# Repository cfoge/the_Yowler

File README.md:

# the_Yowler
If you find this usefull and would like to pay it forward you can do so here 
XXXXXXXXXXXXXXXXXXXXXXXXXXXXXXXX

WARNING!!!!! Please be aware of the risks asociated with electronics and take the relivant percautuions.

XXXXXXXXXXXXXXXXXXXXXXXXXXXXXXXX

An open source noise maker that saw its life as a Kickstarter product in 2017 and has now become open.

[Mouser BOM cart](https://au.mouser.com/ProjectManager/ProjectDetail.aspx?AccessID=0d14517efb)

The design originates from this kickstarter: https://www.kickstarter.com/projects/218568730/the-yowler-a-community-built-diy-noise-synth
and features:
4 square wave oscilators with knobs and switchible ldr's
3 xor gates used to mix the signals
1 primitive vca made from back to back diodes
a rc low pass filter
a decay cap 
trigger button/jack
sterio/mono out
built in speaker

Please use the design files and ideas in this project to make your own stuff, and share your designs and creations with others.
If you come up with any great ideas or mods, please tell me so i can roll good ideas back into the main design.

Cheers

Rob

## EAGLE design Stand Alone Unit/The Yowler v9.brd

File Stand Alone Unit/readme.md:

These are the designs for the standalone (not eurorack or any other system) Yowler noise machine.

The design originates from this kickstarter: https://www.kickstarter.com/projects/218568730/the-yowler-a-community-built-diy-noise-synth
and features:
4 square wave oscilators with knobs and switchible ldr's
3 xor gates used to mix the signals
1 primitive vca made from back to back diodes
a rc low pass filter
a decay cap 
trigger button/jack
sterio/mono out
built in speaker

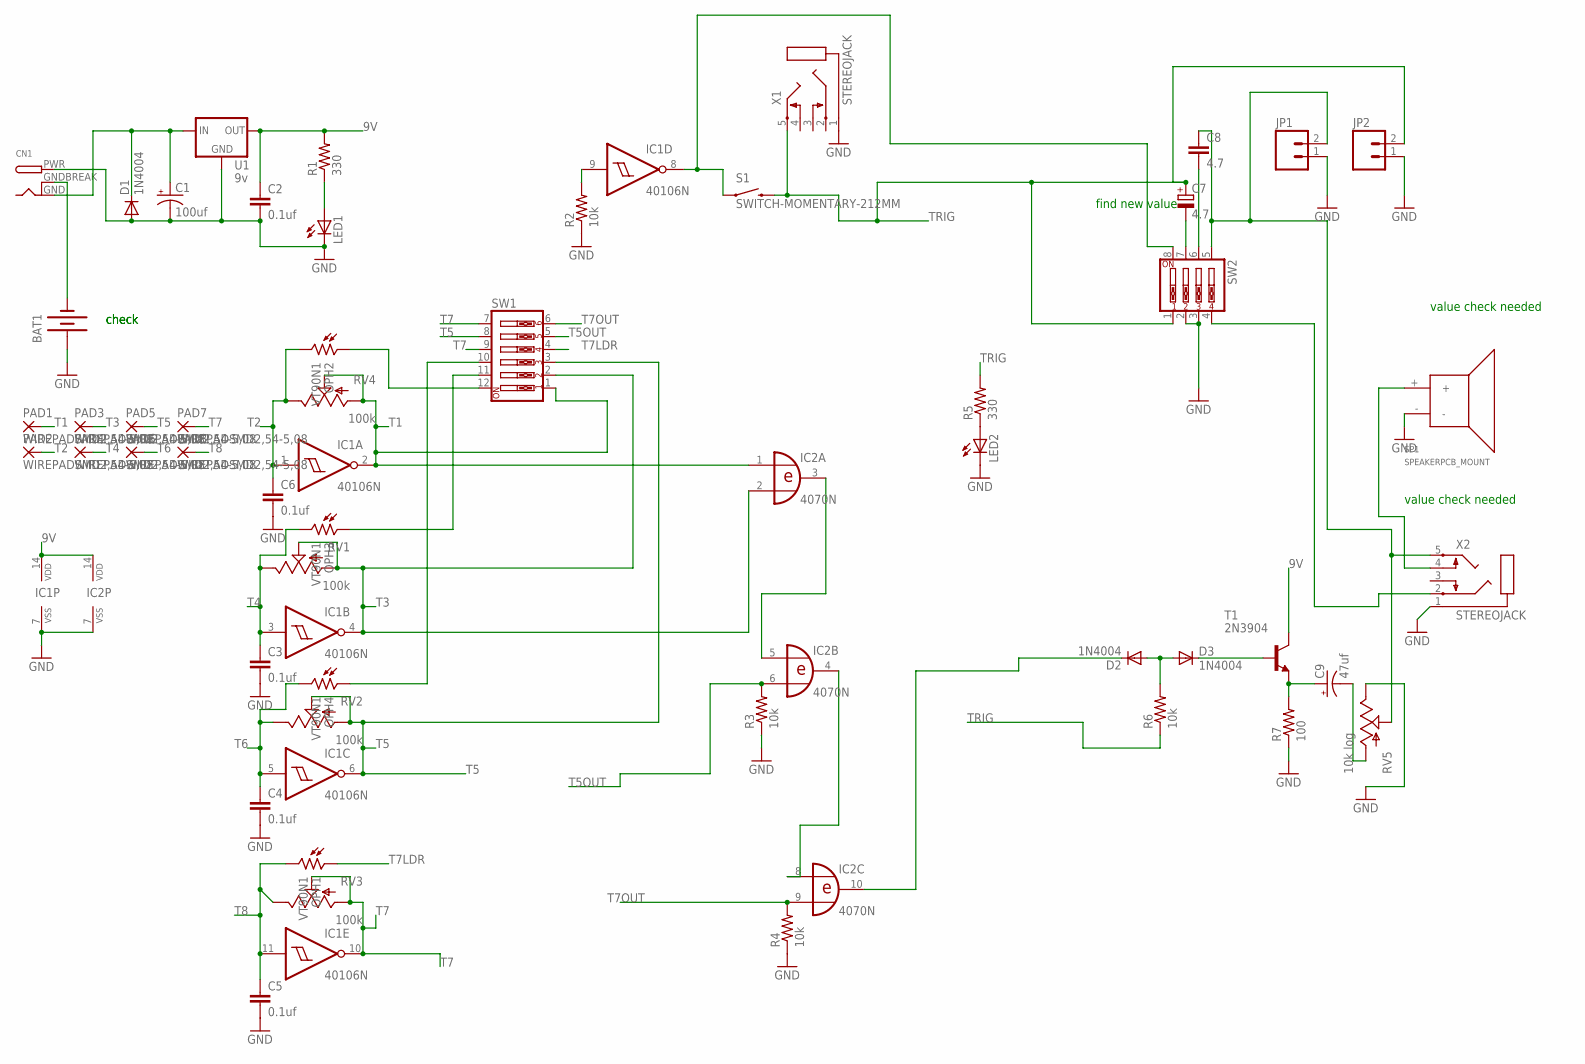
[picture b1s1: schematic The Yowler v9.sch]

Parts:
BAT1: BATTERY9V; BATTCON_9V
C1: 100uf; E5-6
C2, C3, C4, C5, C6: 0.1uf; CAP-PTH-5MM
C7: 4.7; E5-5
C8: 4.7; C050-030X075
C9: 47uf; CPOL-RADIAL-10UF-25V
CN1: DCBARRELPTH; DCJACK_2MM_PTH
D1, D2, D3: 1N4004; DO41-10
IC1: 40106N; DIL14
IC2: 4070N; DIL14
JP1, JP2: M02POGO_PIN_HOLES_ONLY; 1X02_PP_HOLES_ONLY
LED1, LED2: LED3MM
OPH1, OPH2, OPH3, OPH4: VT90N1; VT900
PAD1, PAD2, PAD3, PAD4, PAD5, PAD6, PAD7, PAD8: WIREPADSMD2,54-5,08; SMD2,54-5,08
R1, R5: 330; AXIAL-0.4
R2, R3, R4, R6: 10k; AXIAL-0.4
R7: 100; AXIAL-0.4
RV1, RV2, RV3, RV4: 100k; ALPS_POT
RV5: 10k log; ALPS_POT
S1: SWITCH-MOMENTARY-212MM; TACTILE-PTH-12MM
SP1: SPEAKERPCB_MOUNT; PCB_MOUNT_SPEAKER
SW1: SW_DIP-6; EDG-06
SW2: SW_DIP-4; EDG-04
T1: 2N3904; TO92
U1: 9v; TO-220-ALT
X1, X2: STEREOJACK; STX3100

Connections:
9V: C2.1, IC1.14 (VDD), IC2.14 (VDD), R1.P$2 (2), T1.1 (C), U1.OUT
AUDIO: SW2.4, X2.2
GND: BAT1.+, C1.-, C2.2, C3.2, C4.2, C5.2, C6.2, CN1.PWR, D1.A, IC1.7 (VSS), IC2.7 (VSS), JP1.1, JP2.1, LED1.K (C), LED2.K (C), R2.P$1 (1), R3.P$1 (1), R4.P$1 (1), R7.P$1 (1), RV5.P$1 (E), SP1.-, SW2.2, SW2.3, U1.GND, X1.1, X2.1
unnamed: LED2.A, R5.P$1 (1)
unnamed: IC1.9 (I), R2.P$2 (2)
unnamed: OPH4.1, SW1.10
unnamed: IC2.4 (O), IC2.8 (I0)
unnamed: C9.2 (-), RV5.P$3 (A)
unnamed: C1.+, CN1.GND, D1.C, U1.IN
unnamed: LED1.A, R1.P$1 (1)
unnamed: IC2.3 (O), IC2.5 (I0)
unnamed: OPH2.1, SW1.12
unnamed: IC1.8 (O), S1.1, SW2.8
unnamed: OPH3.1, SW1.11
unnamed: BAT1.-, CN1.GNDBREAK
unnamed: C8.2, SW2.6
unnamed: D2.C, IC2.10 (O)
unnamed: D2.A, D3.A, R6.P$2 (2)
unnamed: C7.-, SW2.7
unnamed: D3.C, T1.2 (B)
unnamed: C9.1 (+), R7.P$2 (2), T1.3 (E)
unnamed: C8.1, JP1.2, RV5.P$2 (S), SW2.5, X2.5
unnamed: SP1.+, X2.4
T1: IC1.2 (O), IC2.1 (I0), PAD1.1, RV4.P$2 (S), RV4.P$3 (A), SW1.1
T2: C6.1, IC1.1 (I), OPH2.2, PAD2.1, RV4.P$1 (E)
T3: IC1.4 (O), IC2.2 (I1), PAD3.1, RV1.P$2 (S), RV1.P$3 (A), SW1.2
T4: C3.1, IC1.3 (I), OPH3.2, PAD4.1, RV1.P$1 (E)
T5: IC1.6 (O), PAD5.1, RV2.P$2 (S), RV2.P$3 (A), SW1.3, SW1.8
T5OUT: IC2.6 (I1), R3.P$2 (2), SW1.5
T6: C4.1, IC1.5 (I), OPH4.2, PAD6.1, RV2.P$1 (E)
T7: IC1.10 (O), PAD7.1, RV3.P$2 (S), RV3.P$3 (A), SW1.7, SW1.9
T7LDR: OPH1.1, SW1.4
T7OUT: IC2.9 (I1), R4.P$2 (2), SW1.6
T8: C5.1, IC1.11 (I), OPH1.2, PAD8.1, RV3.P$1 (E)
TRIG: C7.+, JP2.2, R5.P$2 (2), R6.P$1 (1), S1.3 (2), SW2.1, X1.5

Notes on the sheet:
check
value check needed
find new value

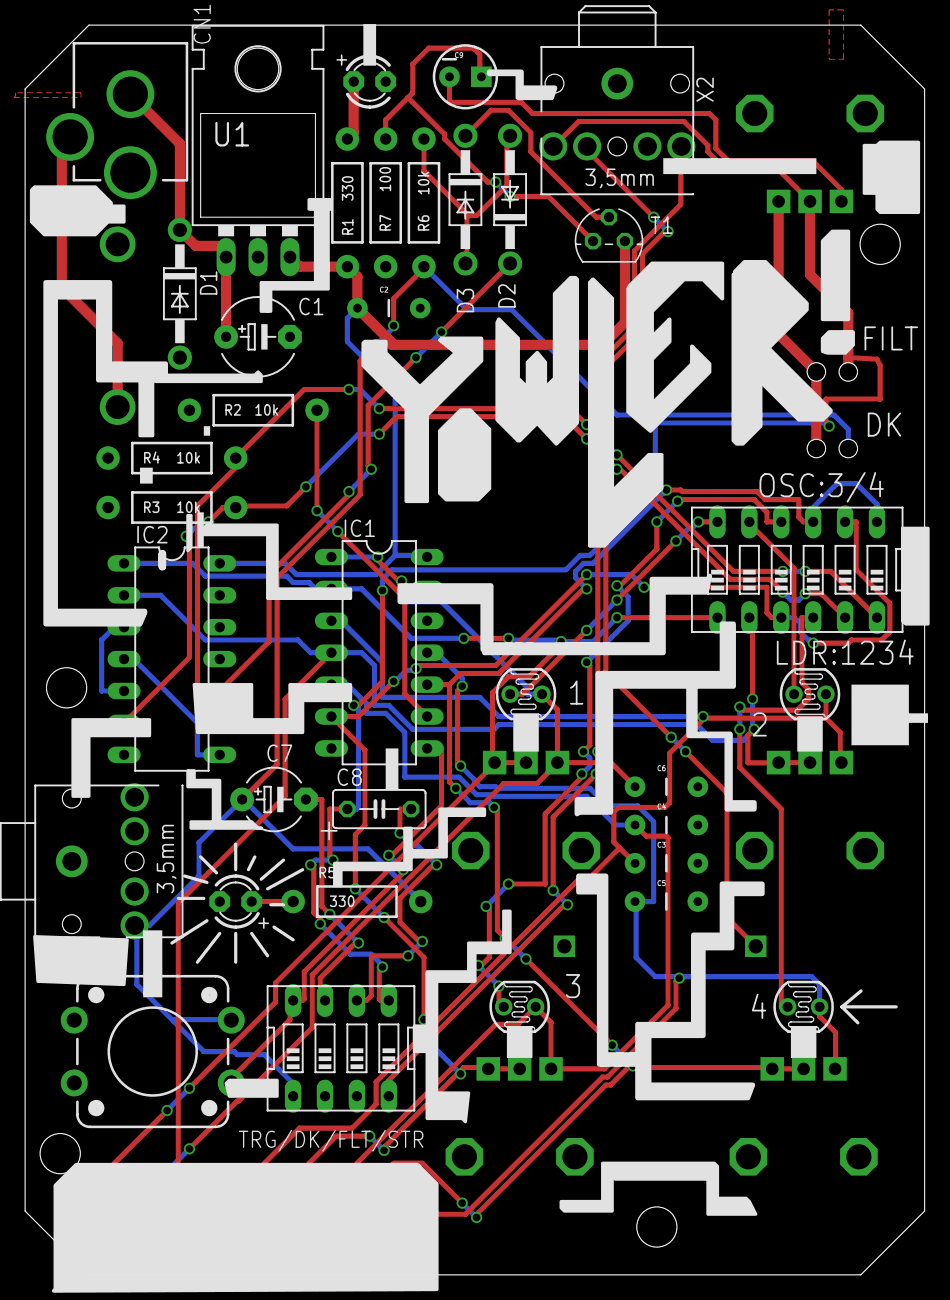
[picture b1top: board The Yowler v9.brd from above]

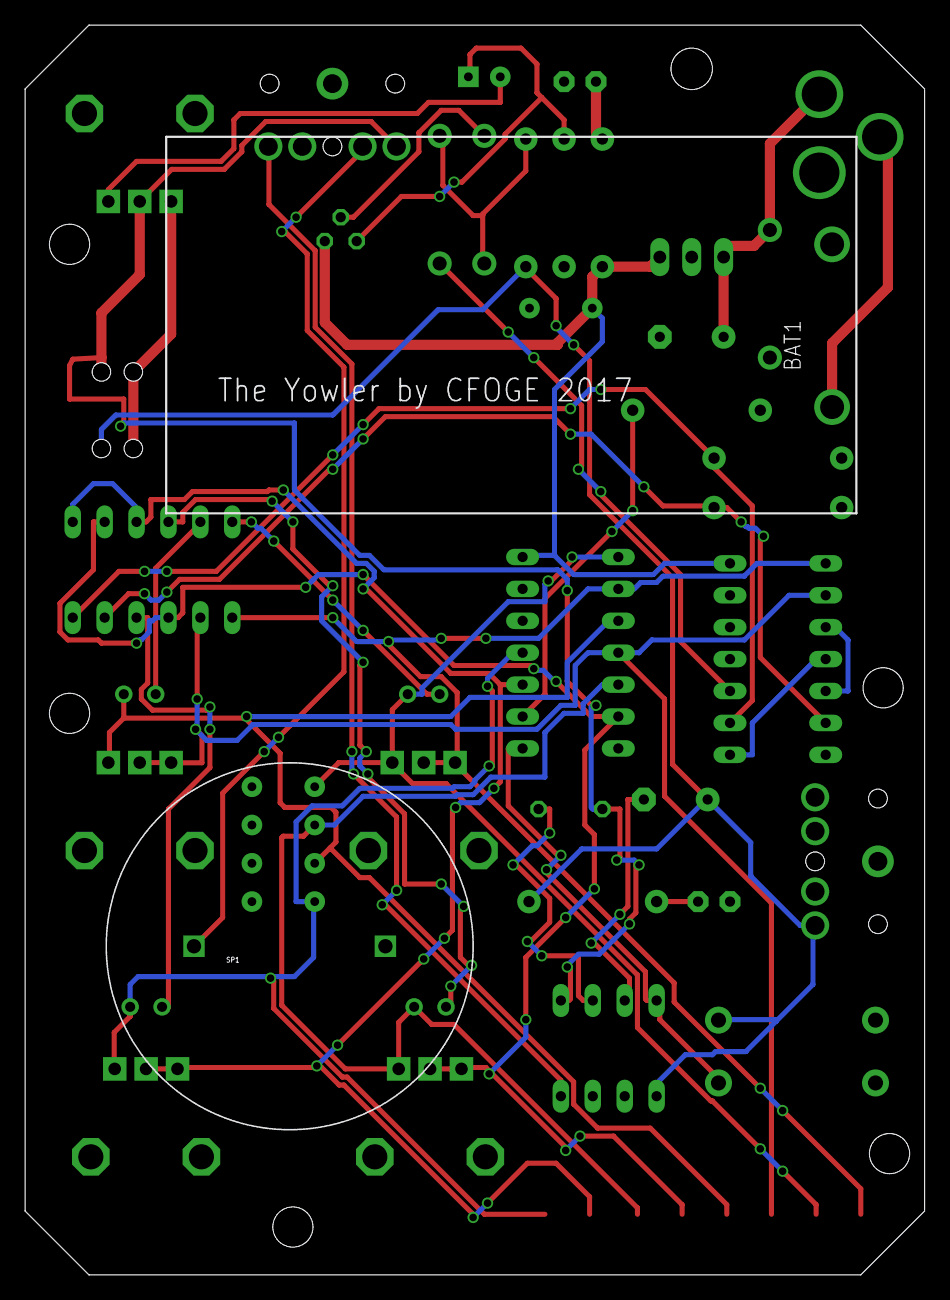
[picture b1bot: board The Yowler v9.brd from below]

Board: 2 copper layers, 71.6 x 99.5 mm, 52 parts (2 on the bottom side), 35 nets.

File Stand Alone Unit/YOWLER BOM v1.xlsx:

YOWLER BOM
Part | VALUE | Number | LINK
BAT1 | 9v batery clip | 1 | http://www.altronics.com.au/p/s5048-9v-battery-holder-pcb-mount/
C1 | 100uf POLARIZED CAPACITOR | 1
C2-C6 | 0.1uf | 5
C7 | 4.7uf POLARIZED CAPACITOR < 50v | 1
C8 | 4.7uf POLARIZED CAPACITOR (ELECTROLITIC) <50v | 1
C9 | 47uf Capacitor Polarized <50v | 1
CN1 | 2.0mm DC Barrel Jack | 1 | http://www.taydaelectronics.com/dc-power-jack-2-1mm-barrel-t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
D1 | 1n4001 | 1 | https://www.taydaelectronics.com/1n4001-diode-1a-50v.html
D2-D3 | 1N4148 | 2 | https://www.taydaelectronics.com/1n4148-switching-signal-diode.html
Dip14 | 14 pin ic socket | 2 | https://www.taydaelectronics.com/14-pin-dip-ic-socket-adapto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
IC1 | 40106N Hex SCHMITT TRIGGER | 1 | https://www.taydaelectronics.com/cd40106-cd40106be-40106-hex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
IC2 | 4070N Quad 2-input XOR | 1 | https://www.taydaelectronics.com/cd4070-cd4070be-4070-quad-e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
LED1-LED2 | LED3MM "yellow" | 2 | https://www.taydaelectronics.com/led-3mm-yellow.html
OPH1-OPH4 | VT90N1 100k LDR | 4 | http://www.taydaelectronics.com/photo-conductive-cell-resist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
R1,R5 | 330ohm 1/4w | 2
R2-R4 & R6 | 10kohm 1/4w | 4
R7 | 100ohm 1/4w | 1
RV1-RV5 | 100k POT "ALPS_POT" | 4 | https://www.taydaelectronics.com/100k-ohm-logarithmic-taper-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
RV5 | 10k log | 1 | https://www.taydaelectronics.com/10k-ohm-logarithmic-taper-p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
S1 | SWITCH-MOMENTARY-12MM | 1 | http://www.altronics.com.au/p/s1125-spst-momentary-pcb-mount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
SP1 | SPEAKER PCB_MOUNT COM-11089 | 1 | https://littlebirdelectronics.com.au/products/speaker-pcb-mount | or try Sparkfun in the US
SW1 | SW_DIP-6 | 1 | https://www.taydaelectronics.com/dip-switch-6-positions-gold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
SW2 | SW_DIP-4 | 1 | https://www.taydaelectronics.com/dip-switch-4-positions-gold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
T1 | 2N3904 "NPN TRANSISTOR" | 1 | https://www.taydaelectronics.com/2n3904-npn-general-propose-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
U1 | 9v V_REG 7809 | 1 | https://www.taydaelectronics.com/l7809cv-l7809-7809-voltage-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
X1-X2 | STEREOJACK STX3100 | 2 | http://www.digikey.com.au/product-detail/en/cui-inc/SJ1-3555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
OPTINAL:
KNOBS |  | 4 | http://www.taydaelectronics.com/kn8f-knob-grey.html
BOLTS for case | 12mm M3 | 5
NUTS for case | M3 | 5

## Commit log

2017-07-17 Create Eagle Files
2017-07-19 Create Notes and TO DO

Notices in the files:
parts and their libraries:
SparkFun-Passives: Licensing: Creative Commons ShareAlike 4.0 International - https://creativecommons.org/licenses/by-sa/4.0
